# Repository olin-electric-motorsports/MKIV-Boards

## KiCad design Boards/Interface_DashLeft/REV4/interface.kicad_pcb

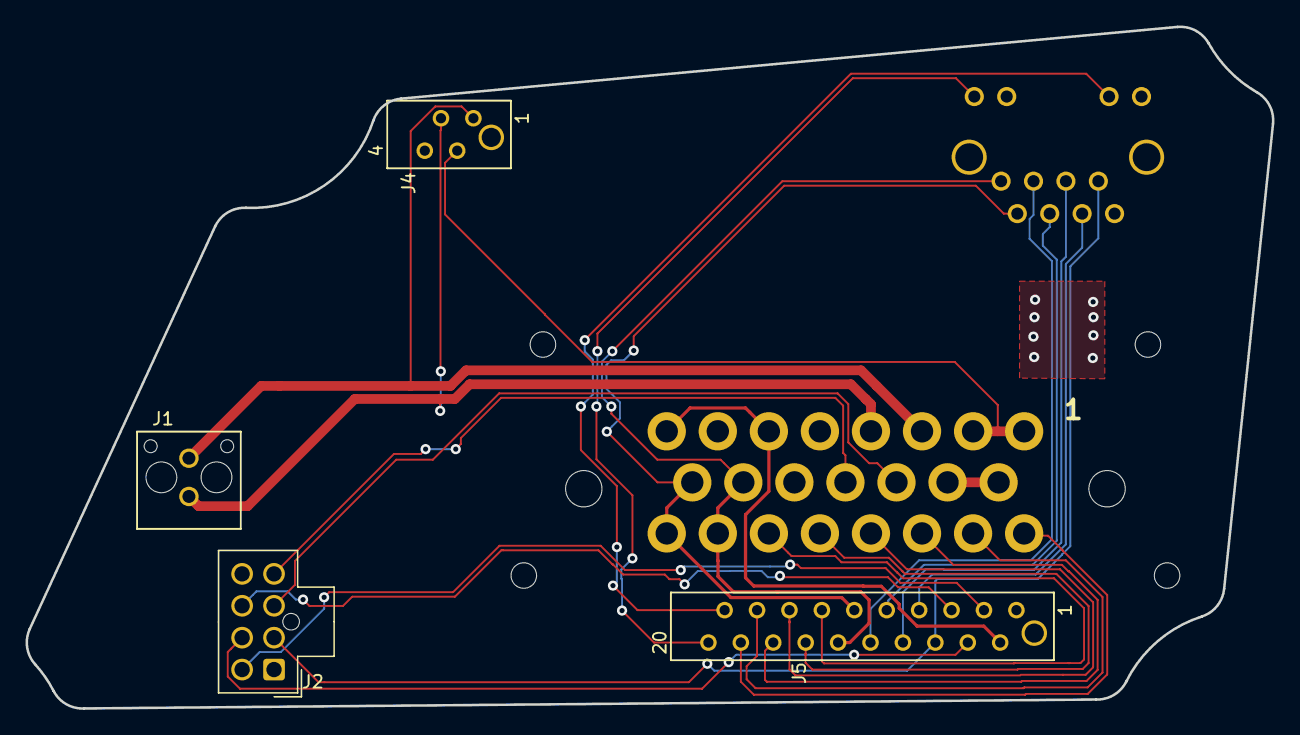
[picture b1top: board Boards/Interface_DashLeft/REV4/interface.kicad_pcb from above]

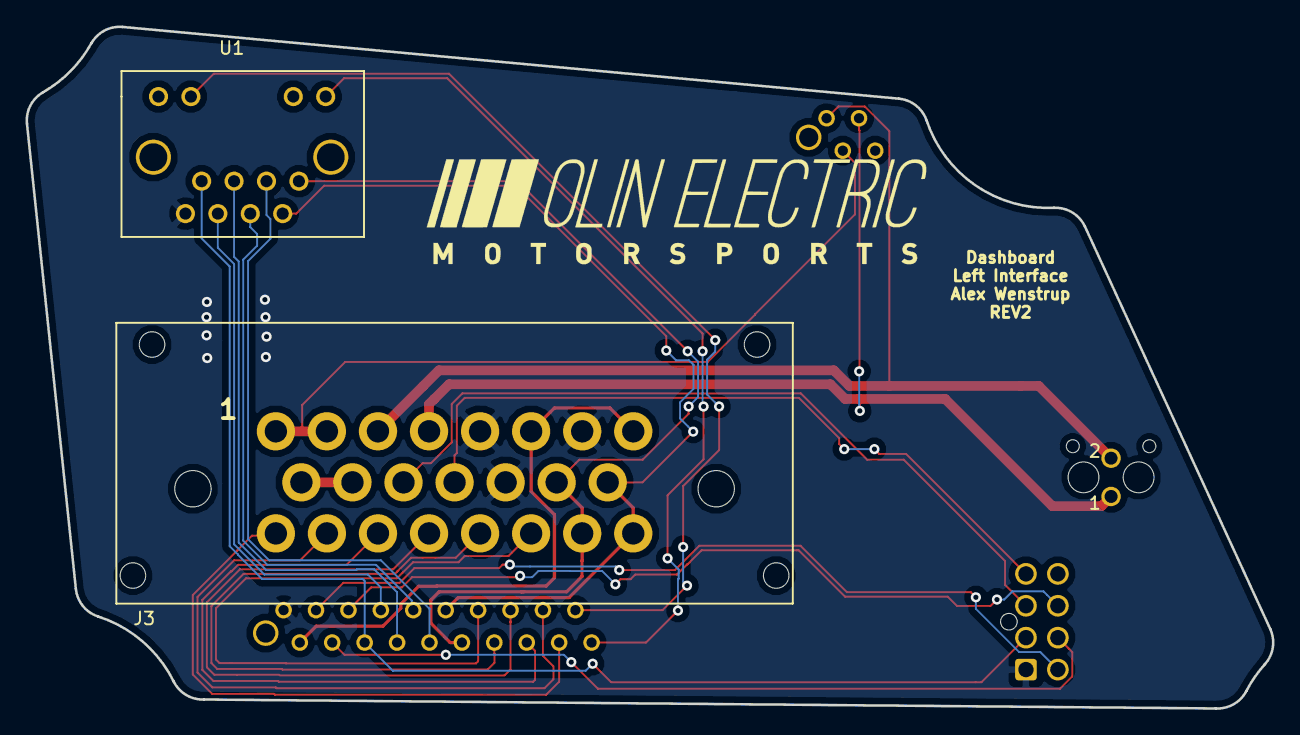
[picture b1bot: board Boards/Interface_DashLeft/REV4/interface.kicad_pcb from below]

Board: 2 copper layers, 97.7 x 53.4 mm, 6 parts (2 on the bottom side), 26 nets.

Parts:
J1: UF_2_VT; MicroFit_V_2
J2: MM_F_VT_08; Molex_Nano-Fit_105310-xx08_2x04_P2.50mm_Vertical
J3: Ampseal_23_VT; Ampseal_23
J4: MM_F_VT_04; micromatch_female_vert_4
J5: MM_F_VT_20; micromatch_female_vert_20
U1: RJ45_VT; RJ45-Vertical

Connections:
/5V: J2.2, J5.6, U1.7
/12V: J3.6, J3.8, J5.2
/BOTS->ESTOP: J1.2, J3.3, J4.1
/BSPD->IS: J3.9, J3.10
/CANH: J3.15, J3.23, J5.11, U1.2
/CANL: J3.14, J3.22, J5.12, U1.1
/Drive_Select+: J2.5, J5.3
/Drive_Select-: J2.7, J5.5
/Drive_Select_Sense: J2.6, J5.4
/ESTOP->HVD: J1.1, J3.4, J4.3
/GND: J2.1, J3.5, J3.7, J3.13, J5.1, U1.8
/IS->BOTS: J3.1, J3.2, J4.2
/LED1: J5.19, U1.10
/LED2: J5.20, U1.12
/MISO: J5.8, U1.5
/MOSI: J5.7, U1.6
/RESET: J5.10, U1.3
/SCK: J5.9, U1.4
/SCL: J2.4, J3.12
/SDA: J2.3, J3.11
/Throttle1+: J3.21, J5.13
/Throttle1-: J3.19, J5.15
/Throttle1_Sense: J3.20, J5.14
/Throttle2+: J3.18, J5.16
/Throttle2-: J3.16, J5.18
/Throttle2_Sense: J3.17, J5.17

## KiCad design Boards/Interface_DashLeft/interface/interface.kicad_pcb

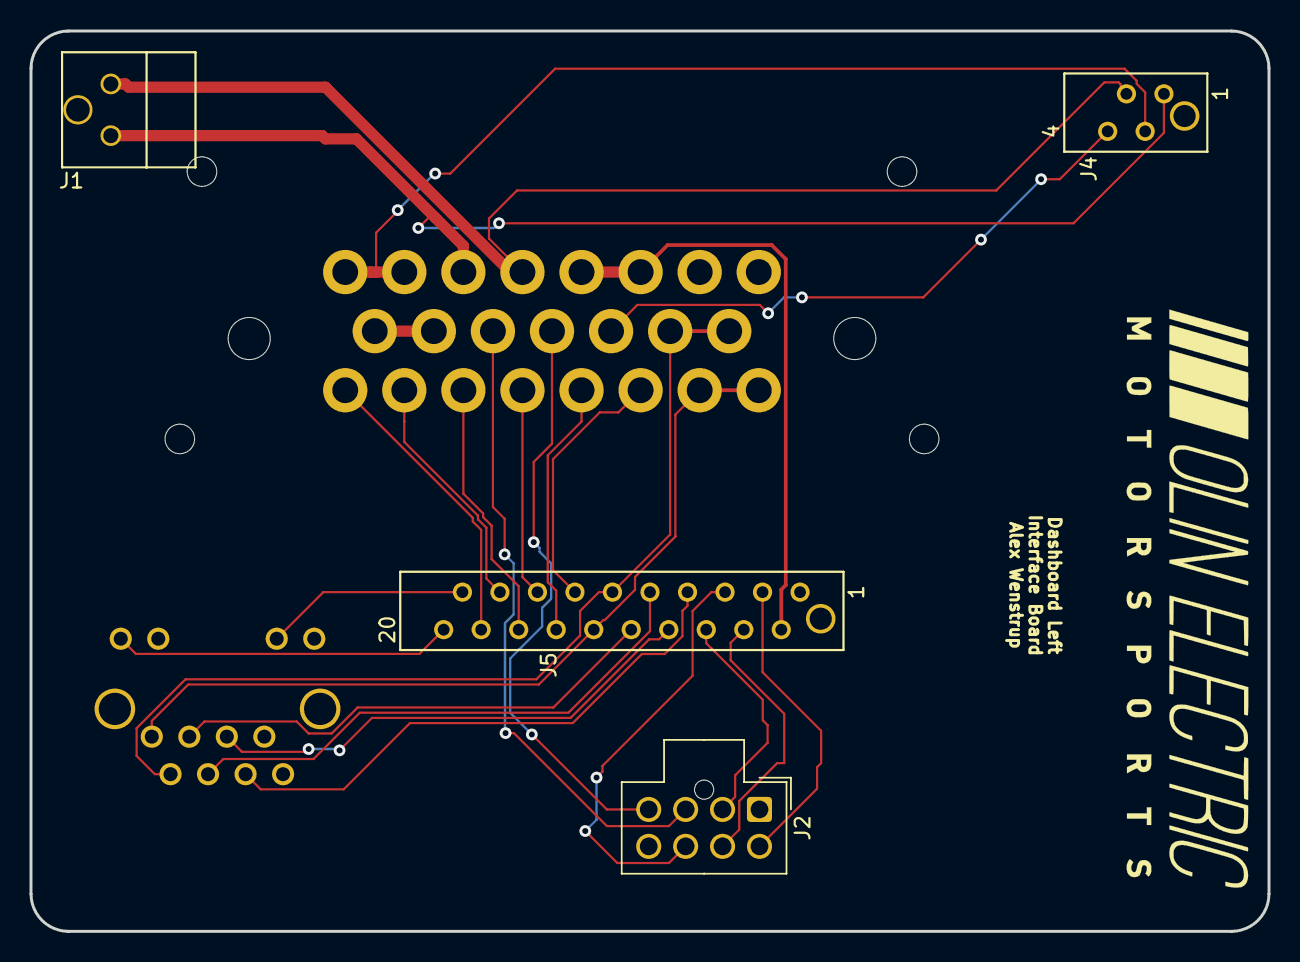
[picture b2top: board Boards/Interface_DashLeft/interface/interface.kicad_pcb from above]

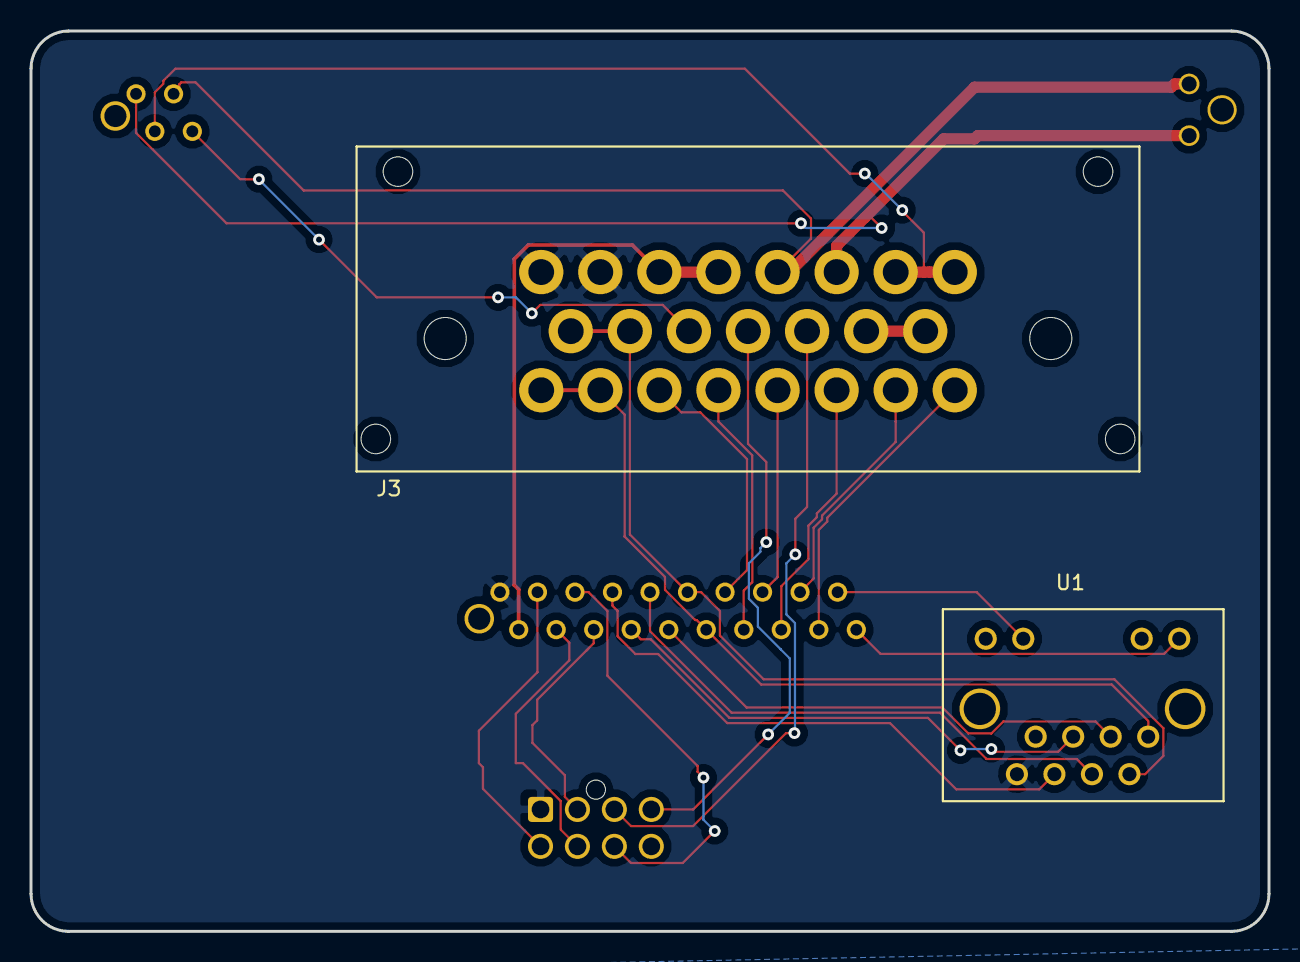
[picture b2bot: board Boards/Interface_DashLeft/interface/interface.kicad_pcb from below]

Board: 2 copper layers, 83.8 x 61.0 mm, 6 parts (2 on the bottom side), 27 nets.

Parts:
J1: UF_2_VT; Ultrafit_2
J2: MM_F_VT_08; Molex_Nano-Fit_105310-xx08_2x04_P2.50mm_Vertical
J3: Ampseal_23_VT; Ampseal_23
J4: MM_F_VT_04; micromatch_female_vert_4
J5: MM_F_VT_20; micromatch_female_vert_20
U1: RJ45_VT; RJ45-Vertical

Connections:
/5V: J2.2, J5.6
/12V: J3.3, J3.4, J5.2
/BOTS->ESTOP: J1.2, J3.6, J4.1
/BSPD->IS: J3.14, J3.15
/CANH: J3.9, J3.10, J5.11, U1.2
/CANL: J3.16, J3.17, J5.12, U1.1
/Drive_Select+: J2.5, J5.3
/Drive_Select-: J2.7, J5.5
/Drive_Select_Sense: J2.6, J5.4
/ESTOP->HVD: J1.1, J3.5, J4.3
/GND: J2.1, J3.1, J3.2, J5.1, U1.8
/IS->BOTS: J3.7, J3.8, J4.2
/LED1: J5.19, U1.10
/LED2: J5.20, U1.12
/MISO: J5.8, U1.5
/MOSI: J5.7, U1.6
/RESET: J5.10, U1.3
/RTD_LSD_GND: J3.11, J4.4
/SCK: J5.9, U1.4
/SCL: J2.4, J3.12
/SDA: J2.3, J3.13
/Throttle1+: J3.18, J5.13
/Throttle1-: J3.20, J5.15
/Throttle1_Sense: J3.19, J5.14
/Throttle2+: J3.21, J5.16
/Throttle2-: J3.23, J5.18
/Throttle2_Sense: J3.22, J5.17

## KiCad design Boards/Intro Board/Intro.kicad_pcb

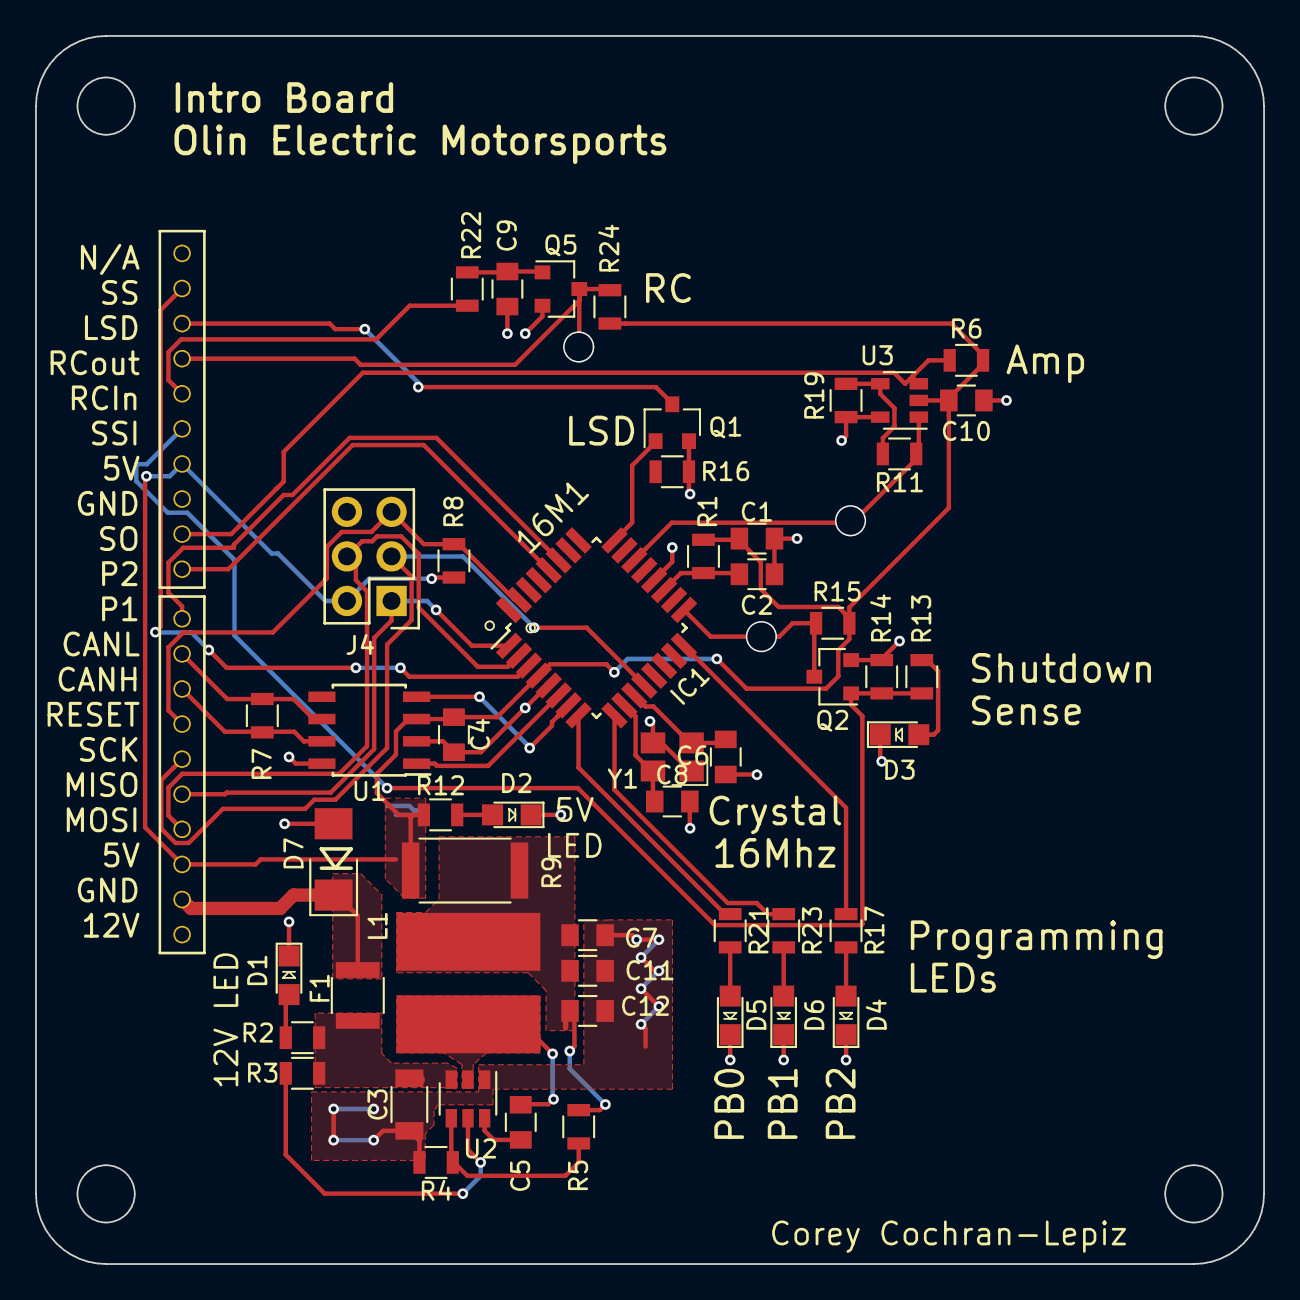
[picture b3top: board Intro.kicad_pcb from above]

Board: 2 copper layers, 70.0 x 70.0 mm, 53 parts (0 on the bottom side), 42 nets.

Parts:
C1, C4, C5, C10, C12: C_0.1uF; C_0805_OEM
C2: C_100pF; C_0805_OEM
C3: C_22uF; C_1206_OEM
C6, C8: C_30pF; C_0805_OEM
C7, C9: C_47uF; C_0805_OEM
C11: C_1uF; C_0805_OEM
D1, D2, D3, D4, D5, D6: LED_0805; LED_0805_OEM
D7: D_Zener_18V; DO-214AA
F1: 500mA; Fuse_1210
IC1: ATMEGA16M1; TQFP-32_7x7mm_Pitch0.8mm
J1, J2: Conn_01x10; CONN RECEPT 2MM VERT AU 10POS
J4: CONN_02X03; Pin_Header_Straight_2x03
L1: L_4.7uH; 4.7uH_Inductor_OEM
Q1, Q2, Q5: SSM3K333R; SOT-23F
R1: R_100; R_0805_OEM
R2, R11, R13, R19: R_1k; R_0805_OEM
R3, R4, R8, R15, R24: R_10k; R_0805_OEM
R5: R_55.1k; R_0805_OEM
R6: R_1M; R_0805_OEM
R7, R12, R17, R21, R23: R_200; R_0805_OEM
R9: R_0_Jumper; R_2512_OEM
R14, R16, R22: R_100k; R_0805_OEM
U1: CAN_Transceiver; SOIC-8_3.9x4.9mm_Pitch1.27mm_OEM
U2: TPS561201; SOT-23-6_OEM
U3: MCP6001RT; SOT-23-5_OEM
Y1: Crystal_SMD; Crystal_SMD_FA238

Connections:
+12V: D7.1, F1.1, J1.9
/12V_Fused: C3.1, F1.2, R2.1, R3.1, U2.3
/CANH: J1.3, R7.1, U1.7
/CANL: J1.2, R7.2, U1.6
/LSD: J2.3, Q1.3
/LSD_Gate: IC1.24, Q1.1
/MISO: IC1.1, J1.6, J4.1
/MOSI: IC1.2, J1.7, J4.4
/P_LED_1: IC1.8, R21.1
/P_LED_2: IC1.9, R23.1
/P_LED_3: IC1.16, R17.1
/Pinout1: IC1.27, J1.1
/Pinout2: IC1.28, J2.10
/RCIn: J2.5, R22.1
/RCOut: J2.4, Q5.3, R24.2
/RESET: IC1.31, J1.4, J4.5, R8.2
/RXCAN: IC1.7, U1.4
/SCK: IC1.12, J1.5, J4.3
/SS: IC1.3, J2.2
/SSI_1: J2.6, Q2.1, R13.1, R14.1
/SSO_1: IC1.17, Q2.3, R15.2
/SensorAmp: IC1.22, R11.1, U3.1
/SensorOut: J2.9, R6.2, U3.3
/TXCAN: IC1.6, U1.1
GND: C1.2, C2.2, C3.2, C4.2, C6.2, C7.2, C8.2, C9.1, C10.1, C11.2, C12.2, D1.1, D2.1, D3.1, D4.1, D5.1, D6.1, D7.2, IC1.5, IC1.20, J1.10, J2.8, J4.6, Q1.2, Q2.2, Q5.2, R4.2, R14.2, R16.2, R19.2, U1.2, U1.8, U2.1, U3.5, Y1.2, Y1.4
unnamed: C2.1, IC1.19, R1.2
unnamed: C5.1, U2.6
unnamed: C5.2, L1.1, U2.2
unnamed: C6.1, IC1.11, Y1.1
unnamed: C8.1, IC1.10, Y1.3
unnamed: C9.2, Q5.1, R22.2
unnamed: C7.1, C11.1, C12.1, L1.2, R5.2, R9.2
unnamed: D1.2, R2.2
unnamed: D2.2, R12.2
unnamed: D3.2, R13.2
unnamed: D4.2, R17.2
unnamed: D5.2, R21.2
unnamed: D6.2, R23.2
unnamed: R3.2, U2.5
unnamed: R4.1, R5.1, U2.4
unnamed: R11.2, R19.1, U3.4
VCC: C1.1, C4.1, C10.2, IC1.4, J1.8, J2.7, J4.2, R1.1, R6.1, R8.1, R9.1, R12.1, R15.1, R24.1, U1.3, U3.2

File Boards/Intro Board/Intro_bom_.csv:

Component,Description,Part,References,Value,Footprint,Quantity Per PCB,Datasheet,Package,MPN,MFN,PurchasingLink,Purchase_Link
1,"Capacitor, 0.1uF, 50V, 5%, 0805",C_0.1uF,C1 C4 C5 C10 C12,C_0.1uF,C_0805_OEM,5,http://datasheets.avx.com/X7RDielectric.pdf,Value,478-3352-1-ND,Digi-Key,https://www.digikey.com/products/en?keywords=478-3352-1-ND,
2,"Capacitor, 100pF, 50V, 5%, 0805",C_100pF,C2,C_100pF,C_0805_OEM,1,https://content.kemet.com/datasheets/KEM_C1003_C0G_SMD.pdf,Value,399-1122-1-ND,Digi-Key,https://www.digikey.com/product-detail/en/kemet/C0805C101J5G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,
3,"Capacitor, 1uF, 25V, 10%, 0805",C_1uF,C11,C_1uF,C_0805_OEM,1,http://datasheets.avx.com/X7RDielectric.pdf,Value,478-10487-1-ND,Digi-Key,https://www.digikey.com/product-detail/en/avx-corporation/08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,
4,"Capacitor, 22uF, 16V, 20%, 1206",C_22uF,C3,C_22uF,C_1206_OEM,1,http://www.samsungsem.com/kr/support/product-search/mlcc/__i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,Value,1276-2725-1-ND,Digi-Key,https://www.digikey.com/products/en?keywords=1276-2725-1-ND,
5,"Capacitor, 30pF, 50V, 5%, 0805",C_30pF,C6 C8,C_30pF,C_0805_OEM,2,https://media.digikey.com/pdf/Data%20Sheets/Samsung%20PDFs/C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,Value,1276-1130-1-ND,Digi-Key,https://www.digikey.com/product-detail/en/samsung-electro-me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,
6,"Capacitor, 47uF, 6.3V, 20%, 0805",C_47uF,C7 C9,C_47uF,C_0805_OEM,2,http://www.yuden.co.jp/productdata/catalog/en/mlcc_all_e.pdf,Value,587-4280-1-ND,Digi-Key,https://www.digikey.com/product-detail/en/taiyo-yuden/JMK212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,
7,"Diode, Zener, 18V, 5W, 5%",D_Zener_18V,D7,D_Zener_18V,DO-214AA,1,http://www.mccsemi.com/up_pdf/SMBJ5338B-SMBJ5388B(SMB).pdf,DO-214AA (SMB),SMBJ5355B-TPMSCT-ND,Digi-Key,https://www.digikey.com/products/en?keywords=SMBJ5355B-TPMSCT-ND,
8,"LED, Green, 2.2V, 20mA, 0805",LED_0805,D1 D2 D3 D4 D5 D6,LED_0805,LED_0805_OEM,6,http://www.osram-os.com/Graphics/XPic9/00078860_0.pdf,Value,475-1410-1-ND,Digi-Key,https://www.digikey.com/products/en?keywords=475-1410-1-ND,
9,"Fuse, PTC, 500mA, 16V, 1210",F_500mA_16V,F1,500mA,Fuse_1210,1,https://belfuse.com/resources/CircuitProtection/datasheets/0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,Value,507-1786-1-ND,Digi-Key,https://www.digikey.com/product-detail/en/bel-fuse-inc/0ZCH0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,
10,"Microcontroller, 8-bit, 1KB RAM, 16KB Flash",ATMEGA16M1,IC1,ATMEGA16M1,TQFP-32_7x7mm_Pitch0.8mm,1,http://www.atmel.com/Images/Atmel-8209-8-bit%20AVR%20ATmega1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,Value,ATMEGA16M1-AU-ND,Digi-Key,https://www.digikey.com/product-detail/en/atmel/ATMEGA16M1-A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,
11,"Connector header through hole 2x3 0.100"" (2.54mm)",CONN_02X03,J4,CONN_02X03,Pin_Header_Straight_2x03,1,http://portal.fciconnect.com/Comergent//fci/drawing/67996.pdf,Value,609-3234-ND,Digi-Key,https://www.digikey.com/product-detail/en/amphenol-fci/67997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,
12,"Generic connector, single row, 01x10, script generated (kicad-library-utils/schlib/autogen/connector/)",Conn_01x10,J1 J2,Conn_01x10,CONN RECEPT 2MM VERT AU 10POS,2,~,,,,,
13,"Inductor, 4.7uH, 4.4A, 25mOhm, 20%",L_4.7uH,L1,L_4.7uH,4.7uH_Inductor_OEM,1,https://product.tdk.com/info/en/documents/wdcatalog/withdraw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,Value,445-6583-1-ND,Digi-Key,https://www.digikey.com/product-detail/en/tdk-corporation/VL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,
14,"MOSFET, N-channel, 30V, 6A",SSM3K333R,Q1 Q2 Q5,SSM3K333R,SOT-23F,3,https://drive.google.com/drive/folders/0B-V-iZf33Y4GNzhDQTJZanJRbVk,SOT-23-3 Flat Leads,SSM3K333RLFCT-ND,Digi-Key,https://www.digikey.com/product-detail/en/toshiba-semiconduc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,https://www.digikey.com/product-detail/en/toshiba-semiconduc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
15,,R_0_Jumper,R9,R_0_Jumper,R_2512_OEM,1,http://www.te.com/commerce/DocumentDelivery/DDEController?Ac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,Value,A121322CT-ND,Digi-Key,https://www.digikey.com/products/en?keywords=A121322CT-ND,
16,"Resistor, 100, 0.25W, 1%, 0805",R_100,R1,R_100,R_0805_OEM,1,https://www.seielect.com/Catalog/SEI-rncp.pdf,Value,RNCP0805FTD100RCT-ND,Digi-Key,https://www.digikey.com/products/en?keywords=RNCP0805FTD100RCT-ND,
17,,R_100k,R14 R16 R22,R_100k,R_0805_OEM,3,http://www.yageo.com.tw/exep/pages/download/literatures/PYu-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,Value,311-100KCRCT-ND,Digi-Key,https://www.digikey.com/products/en?keywords=311-100KCRCT-ND,
18,,R_10k,R3 R4 R8 R15 R24,R_10k,R_0805_OEM,5,http://www.bourns.com/data/global/pdfs/CRS.pdf,Value,CRS0805-FX-1002ELFCT-ND,Digi-Key,https://www.digikey.com/products/en?keywords=CRS0805-FX-1002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,
19,"Resistor, 1M, 0.125W, 5%, 0805",R_1M,R6,R_1M,R_0805_OEM,1,https://www.seielect.com/Catalog/SEI-rncp.pdf,Value,RMCF0805JT1M00CT-ND,Digi-Key,https://www.digikey.com/product-detail/en/stackpole-electron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,
20,,R_1k,R2 R11 R13 R19,R_1k,R_0805_OEM,4,https://www.seielect.com/Catalog/SEI-rncp.pdf,Value,RNCP0805FTD1K00CT-ND,Digi-Key,https://www.digikey.com/products/en?keywords=RNCP0805FTD1K00CT-ND,
21,"Resistor, 200, 0.125W, 5%, 0805",R_200,R7 R12 R17 R21 R23,R_200,R_0805_OEM,5,https://www.seielect.com/Catalog/SEI-RMCF_RMCP.pdf,Value,RMCF0805JT200RCT-ND,Digi-Key,https://www.digikey.com/products/en?keywords=RMCF0805JT200RCT-ND,
22,,R_55.1k,R5,R_55.1k,R_0805_OEM,1,http://www.yageo.com.tw/exep/pages/download/literatures/PYu-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,Value,311-51.1KCRCT-ND,Digi-Key,https://www.digikey.com/products/en?keywords=311-51.1KCRCT-ND,
23,,CAN_Transceiver,U1,CAN_Transceiver,SOIC-8_3.9x4.9mm_Pitch1.27mm_OEM,1,http://www.microchip.com/mymicrochip/filehandler.aspx?ddocna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,Value,MCP2561-E/SN-ND,Digi-Key,https://www.digikey.com/products/en?keywords=mcp2561-e%2Fsn,
24,,MCP6001RT,U3,MCP6001RT,SOT-23-5_OEM,1,http://ww1.microchip.com/downloads/en/DeviceDoc/21733j.pdf,,MCP6001RT-I/OTCT-ND,Digi-Key,https://www.digikey.com/product-detail/en/microchip-technolo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,
25,"Buck converter, 4.5-17V input, adj 0.76-7V output, 1A, 580kHz",TPS561201,U2,TPS561201,SOT-23-6_OEM,1,http://www.ti.com/lit/ds/symlink/tps561201.pdf,Value,TPS561201,Digi-Key,https://www.digikey.com/products/en?keywords=296-46928-1-ND,
26,CRYSTAL 16.0000MHZ 18PF SMD,Crystal_SMD,Y1,Crystal_SMD,Crystal_SMD_FA238,1,https://support.epson.biz/td/api/doc_check.php?dl=brief_FA-2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,Value,SER3686CT-ND,Digi-Key,https://www.digikey.com/products/en?keywords=SER3686CT-ND,





Component Groups:,26
Component Count:,53
Fitted Components:,53
Number of PCBs:,1
Total components:,53
Schematic Version:,
Schematic Date:,
BoM Date:,Thu 27 Sep 2018 10:53:54 PM EDT
Schematic Source:,/home/corey/Desktop/Formula/MKIV/Boards/Intro Board/Intro.sch
KiCad Version:,Eeschema 5.0.0-fee4fd1~66~ubuntu18.04.1

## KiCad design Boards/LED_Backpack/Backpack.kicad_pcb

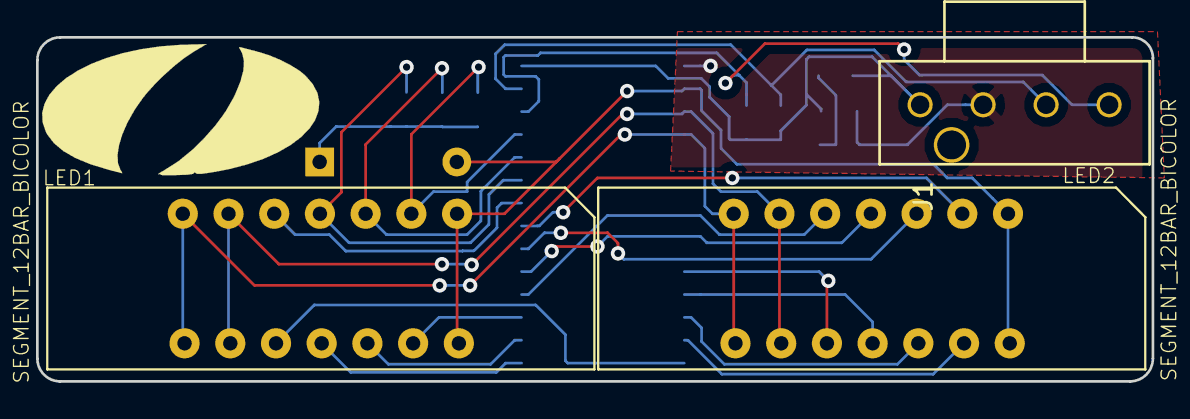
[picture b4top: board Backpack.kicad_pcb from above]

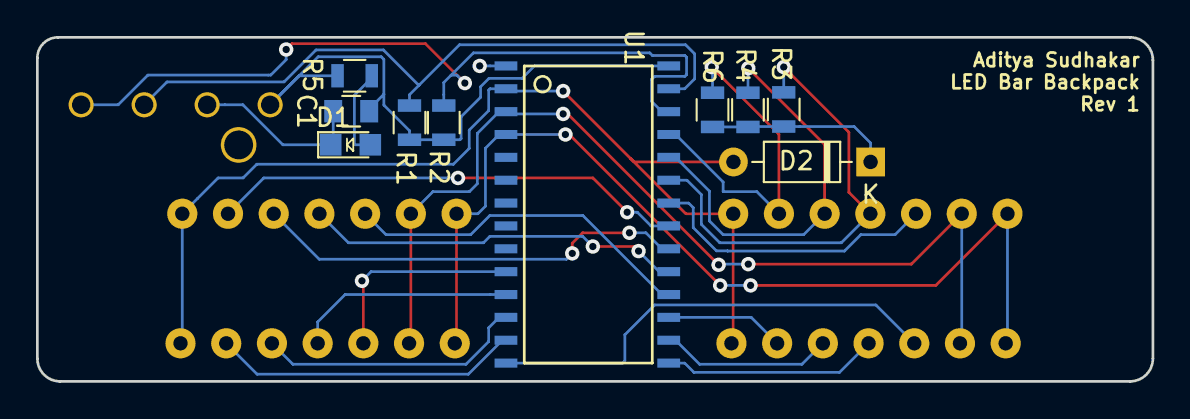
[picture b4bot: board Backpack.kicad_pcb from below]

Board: 2 copper layers, 62.0 x 19.1 mm, 13 parts (10 on the bottom side), 25 nets.

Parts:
C1: C_10uF; C_0805_OEM
D1: LED; LED_0805_OEM
D2: D_Zener_13V; D_DO-35_SOD27_P7.62mm_Horizontal
J1: UF_4_VT; Ultrafit_4
LED1, LED2: SEGMENT_12BAR_BICOLOR; SEGMENT_BICOL_BL-AR12Z3010
R1, R2: 10K; R_0805_OEM
R3, R4, R6: R_51.1k; R_0805_OEM
R5: R_500; R_0805_OEM
U1: HT16K33; SOP28

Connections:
+5V: C1.1, J1.1, R1.2, R2.2, R5.1, U1.28
/COM0: D2.2, LED1.1, LED1.14, LED2.1, LED2.14, U1.2
/COM1: LED1.6, LED1.9, LED2.6, LED2.9, U1.3
/COM2: LED1.7, LED1.8, LED2.7, LED2.8, U1.4
/ROW0: LED1.2, R6.1, U1.25
/ROW1: LED1.3, R4.1, U1.24
/ROW2: LED1.4, R3.1, U1.23
/ROW3: LED1.5, U1.22
/ROW4: LED2.2, U1.21
/ROW5: LED2.3, U1.20
/ROW6: LED2.4, U1.19
/ROW7: LED2.5, U1.18
/ROW8: LED1.13, U1.17
/ROW9: LED1.12, U1.16
/ROW10: LED1.11, U1.15
/ROW11: LED1.10, U1.14
/ROW12: LED2.13, U1.13
/ROW13: LED2.12, U1.12
/ROW14: LED2.11, U1.11
/ROW15: LED2.10, U1.10
/SCL: J1.4, R2.1, U1.26
/SDA: J1.3, R1.1, U1.27
GND: C1.2, D1.1, J1.2, U1.1
unnamed: D1.2, R5.2
unnamed: D2.1, R3.2, R4.2, R6.2

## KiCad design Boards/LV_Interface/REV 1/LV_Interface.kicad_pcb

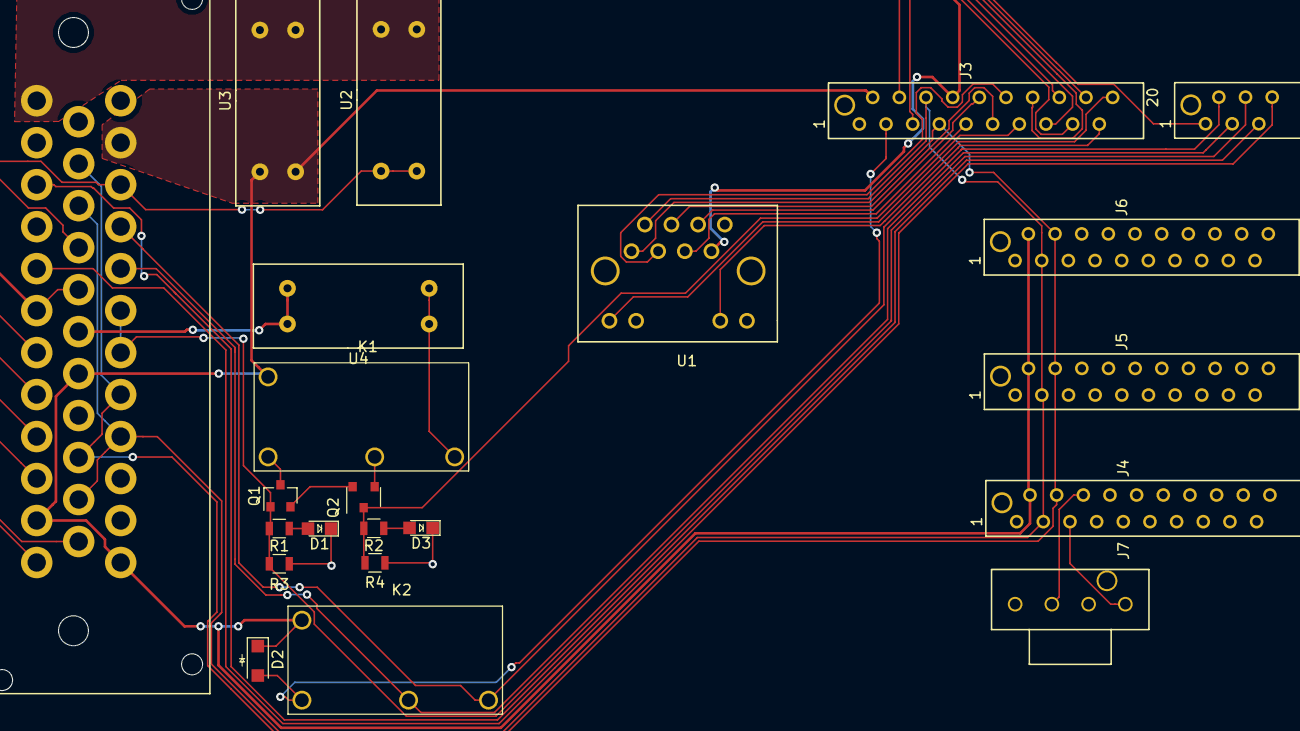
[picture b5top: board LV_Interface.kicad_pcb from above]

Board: 2 copper layers, 22 parts (0 on the bottom side), 35 nets.

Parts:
D1, D3: LED_0805; LED_0805_OEM
D2: SS110LW; D_SOD-123W_OEM
J1: Ampseal_35_VT; Ampseal_35
J2: MM_F_VT_06; micromatch_female_vert_6
J3, J4, J5, J6: MM_F_VT_20; micromatch_female_vert_20
J7: CONN_01x04; Ultrafit_4
K1, K2: G5Q-1A4-DC5-5V; Relay_SPST_OMRON-G5Q-1A4_OEM
Q1: SSM3K333R; SOT-23F
Q2: BSS308PE; SOT-23-3_OEM
R1, R2: R_1K; R_0805_OEM
R3, R4: R_10K; R_0805_OEM
U1: RJ45_VT; RJ45-Vertical
U2, U3, U4: Fuse_Holder_Blade; Fuse_Block_Holder

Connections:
/5V: J1.17, J1.29, J3.8, U1.7
/12V: D2.1, J1.2, J1.12, J1.19, J1.34, J3.2, J4.2, J5.2, J6.2, K1.5, K2.5, U3.2
/BSDP -> IS: J1.5, J2.3, K2.2
/BSPD Current Sense: J1.26, J2.5
/BSPD Relay: D2.2, J3.3, K2.1
/BSPD Switch +: J1.16, J3.18
/Bat +: J1.24, U2.1, U3.1
/Brake Pressure +: J1.32, J3.15
/Brake Pressure -: J1.30, J3.17
/Brake Pressure Sense: J1.31, J3.16
/Brake Switch +: J1.23, J3.4
/Brake Switch -: J1.35, J3.5
/Brakelight LSD: J1.33, J3.14
/CAN high: J1.9, J1.15, J1.22, J3.6, J4.3, J5.3, J6.3, U1.2
/CAN low: J1.8, J1.14, J1.21, J3.7, J4.4, J5.4, J6.4, U1.1
/Cooling Pressure Sense: J1.28, J2.6
/Cooling Pump: J1.18, U4.1
/Cooling Pump LSD: J3.13, Q2.1, R2.2, R4.1
/Cooling Pump Relay: K1.3, U4.2
/Estop -> BSPD: J1.4, J2.2, K2.3
/Fuse -> Estop: J1.3, J2.1, U2.2
/LED 1: J4.5, J7.1
/LED 2: J4.6, J7.3
/MISO: J3.9, U1.5
/MOSI: J3.10, U1.6
/RESET: J3.12, U1.3
/RJ45 LED1: J3.19, U1.10
/RJ45 LED2: J3.20, U1.12
/SCK: J3.11, U1.4
/Shutdown Sense TSMS: J1.6, J1.7, J2.4, Q1.1, R1.2, R3.1
GND: D1.1, D3.1, J1.1, J1.10, J1.11, J1.13, J1.20, J1.25, J1.27, J3.1, J4.1, J5.1, J6.1, J7.2, J7.4, K1.2, Q2.2, R3.2, R4.2, U1.8, U1.9, U1.11, U1.13, U1.14
unnamed: D1.2, R1.1
unnamed: D3.2, R2.1
unnamed: K1.1, Q1.3
unnamed: Q1.2, Q2.3

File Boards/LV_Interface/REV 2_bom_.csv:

Component,Description,Part,References,Value,Footprint,Quantity Per PCB,Datasheet,MPN,MFN,PurchasingLink
1,"LED, Green, 2.2V, 20mA, 0805",LED_0805,D3,LED_0805,LED_0805_OEM,1,http://www.osram-os.com/Graphics/XPic9/00078860_0.pdf,475-1410-1-ND,DK,https://www.digikey.com/products/en?keywords=475-1410-1-ND
2,DIODE SCHOTTKY 100V 1A SOD123W,SS110LW,D2,SS110LW,D_SOD-123W_OEM,1,http://www.taiwansemi.com/products/datasheet/SS14LW%20SERIES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,SS110LWRVGCT-ND,DK,https://www.digikey.com/product-detail/en/taiwan-semiconduct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
3,Ampseal connector 35 pin vertical,Ampseal_35_VT,J1,Ampseal_35_VT,Ampseal_35,1,http://www.te.com/commerce/DocumentDelivery/DDEController?Ac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,1-776231-1,TE,http://www.te.com/usa-en/product-1-776231-1.html
4,CONN HEADER 4 POS 2.54,CONN_01x04,J7,CONN_01x04,Ultrafit_4,1,https://katalog.we-online.de/em/datasheet/6130xx11121.pdf,732-5317-ND,DK,https://www.digikey.com/product-detail/en/wurth-electronics-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
5,Micro-MaTch connector 6 pin female vertical,MM_F_VT_06,J2,MM_F_VT_06,micromatch_female_vert_6,1,http://www.te.com/commerce/DocumentDelivery/DDEController?Ac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,338068-6,TE,http://www.te.com/global-en/product-338068-6.html
6,Micro-MaTch connector 20 pin female vertical,MM_F_VT_20,J3 J4 J5 J6,MM_F_VT_20,micromatch_female_vert_20,4,http://www.te.com/commerce/DocumentDelivery/DDEController?Ac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,2-338068-0,TE,http://www.te.com/global-en/product-2-338068-0.html
7,"Relay, SPST-NO, Switch 10A/30V, Coil 40mA/5V",G5Q-1A4-DC5-5V,K1 K2,G5Q-1A4-DC5-5V,Relay_SPST_OMRON-G5Q-1A4_OEM,2,http://omronfs.omron.com/en_US/ecb/products/pdf/en-g5q.pdf,Z3632-ND,DK,https://www.digikey.com/product-detail/en/omron-electronics-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
8,"MOSFET, P-channel, 30V, 2A",BSS308PE,Q2,BSS308PE,SOT-23-3_OEM,1,https://www.infineon.com/dgdl/BSS308PE_Rev2.03.pdf?folderId=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,BSS308PEH6327XTSA1CT-ND,DK,https://www.digikey.com/products/en/discrete-semiconductor-p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
9,"MOSFET, N-channel, 30V, 6A",SSM3K333R,Q1 Q3,SSM3K333R,SOT-23F,2,https://drive.google.com/drive/folders/0B-V-iZf33Y4GNzhDQTJZanJRbVk,SSM3K333RLFCT-ND,DK,https://www.digikey.com/product-detail/en/toshiba-semiconduc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
10,"Resistor, 10K, 0.25W, 1%, 0805",R_10K,R3 R4,R_10K,R_0805_OEM,2,http://www.bourns.com/data/global/pdfs/CRS.pdf,CRS0805-FX-1002ELFCT-ND,DK,https://www.digikey.com/products/en?keywords=CRS0805-FX-1002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
11,"Resistor, 1K, 0.25W, 1%, 0805",R_1K,R1 R2,R_1K,R_0805_OEM,2,https://www.seielect.com/Catalog/SEI-rncp.pdf,RNCP0805FTD1K00CT-ND,DK,https://www.digikey.com/products/en?keywords=RNCP0805FTD1K00CT-ND
12,Fuse Holder,Fuse_Holder_Blade,U2 U3 U4,Fuse_Holder_Blade,Fuse_Block_Holder,3,https://www.keyelco.com/userAssets/file/M65p41.pdf,36-3557-2-ND ,DK,https://www.digikey.com/product-detail/en/keystone-electroni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
13,RJ45 ethernet connector vertical,RJ45_VT,U1,RJ45_VT,RJ45-Vertical,1,https://www.amphenolcanada.com/ProductSearch/drawings/AC/MRJ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,MRJ-5481-01-ND,DK,https://www.digikey.com/products/en?keywords=MRJ-5481-01
,,,,,,,,,,
,,,,,,,,,,
,,,,,,,,,,
,,,,,,,,,,
,,,,,,,,,,
Component Groups:,13,,,,,,,,,
Component Count:,22,,,,,,,,,
Fitted Components:,22,,,,,,,,,
Number of PCBs:,1,,,,,,,,,
Total components:,22,,,,,,,,,
Schematic Version:,,,,,,,,,,
Schematic Date:,,,,,,,,,,
BoM Date:,Wed 20 Feb 2019 08:30:59 PM EST,,,,,,,,,
Schematic Source:,/home/manu/Desktop/Formula/MKIV-Boards/Boards/LV_Interface/REV 2.sch,,,,,,,,,
KiCad Version:,Eeschema 5.0.0-fee4fd1~66~ubuntu18.04.1,,,,,,,,,
